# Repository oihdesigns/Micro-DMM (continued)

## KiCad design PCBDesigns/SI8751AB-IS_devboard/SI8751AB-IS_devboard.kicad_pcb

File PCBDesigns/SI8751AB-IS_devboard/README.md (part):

# Si8751 AC/DC development board — revision C

KiCad 10 bench prototype targeting **120 V RMS AC / 170 V DC, less than 1 A**, initially with resistive loads. Two SI8751AB-IS drivers operate back-to-back STP12N60M2 MOSFETs. **AMC3330DWER** measures switched voltage with integrated isolated power; **ACS725LLCTR-05AB-T** measures bidirectional load current. The entire board uses one regulated 3.3 V input. All resistors and capacitors are **0805**. The board is two layers, 110 × 90 mm, for 1.6 mm FR-4 and 35 µm copper.

Open `SI8751AB-IS_devboard.kicad_pro`. Reload schematic and board if an earlier revision is still open. Local symbols and footprints, a schematic PDF, BOM, and validation reports/previews are included. Prototype Gerbers and drills are in `fabrication/revC/`. `revision_B_before_3V3_sensor.zip` preserves revision B; the earlier revision A backup is also retained. The inventory workbook was read without modification; existing project preferences were preserved.

## Changes from revision B

- Replaced ACS712-05B with **ACS725LLCTR-05AB-T**, powered from +3V3.
- Removed the 5 V net. J1-7 is **NC**, preserving all other revision B header pin numbers.
- Removed R15/R16, the 2:1 current-output divider. J1-8 now receives the sensor output directly.
- C17 remains 100 nF; the ACS725 internal filter resistance gives approximately 884 Hz bandwidth. C18 is a direct 1 nF output load.
- Current conversion at nominal supply is now **I = (Vout − 1.65 V) / 0.264 V/A**.
- All passives remain 0805. The ACS725 was not found in the supplied purchase history and is a new procurement item.

## Earlier changes: revision A to B

- Added ACS712-05B between Q2 drain and J3 line. Positive current flows toward the load.
- Replaced AMC0330R with AMC3330. Removed SCT01F03S05, TPS70933 and the converter slot. U3/U4 and C9/C10 references are retired.
- Expanded J1 from 5 to 10 pins. **Pin 5 changed from ground to OUTN.** Voltage-interface firmware scaling also changed.
- Added regulated 5 V input, current filtering, 2:1 current-output attenuation, and AMC diagnostic output.
- Changed voltage divider to stocked 1 MΩ / 15 kΩ parts and EN pull-downs to stocked 75 kΩ parts.
- Corrected plated-pad solder-mask serialization in the generator; both mask openings are verified in the saved board.

## Connections

| Pin | Function |
|---|---|
| J1-1 | Regulated +3.3 V input; provide at least 100 mA capacity |
| J1-2 | Logic ground |
| J1-3 | EN, 3.3 V active high; both MOSFETs commanded together |
| J1-4 | VOUT_P, AMC positive differential output |
| J1-5 | VOUT_N, AMC negative differential output; **not ground** |
| J1-6 | Logic ground |
| J1-7 | NC, no connection; formerly the 5 V input in revision B |
| J1-8 | IOUT_ADC, direct ACS725 output referenced to logic ground |
| J1-9 | DIAG_N, AMC status, 10 kΩ pull-up to 3.3 V; LOW means invalid measurement |
| J1-10 | Logic ground |
| J2-1 / J2-2 | Source line / source return |
| J3-1 / J3-2 | Switched line / load return |

The regulated 3.3 V supply returns to GND_LOGIC, which must remain separate from GND_LOAD_RETURN and SOURCE_FLOAT. The ACS725 requires 3.0–3.6 V; do not power the board from 5 V. Power the host ADC with the board to avoid back-powering an unpowered ADC through the current output. J1-7 is unused; supply power at J1-1.

J2/J3 are Wuerth **691311400102**, 7.62 mm headers. Two **691351400002** cable plugs are additional assembly items outside the fitted PCB BOM. [Wuerth mating series](https://www.we-online.com/en/components/products/TBL_7_62_3514_VERTICAL_69135140000X).

## Switching circuit

```text
J2 LINE -- D Q1 S -- SOURCE_FLOAT -- S Q2 D -- ACS725 IP+ to IP- -- J3 LINE
             G1                         G2
             |                          |
          U1 GATE                    U2 GATE
          U1 SOURCE ---- SOURCE_FLOAT --- U2 SOURCE
J2 RETURN ---------------- GND_LOAD_RETURN -------------------- J3 RETURN
```

Opposing body diodes block either polarity when both gates are off. Driver gate outputs are separate. R1/R3 are 100 Ω input resistors, R2/R4 are 75 kΩ default-off pull-downs, and R5/R6 set TT to 10 kΩ. C3/C4 are 10 pF, 1 kV C0G drain-to-MCAP1 capacitors; MCAP2 is unused. A conventional gate/source bleed resistor would overload the weak generated gate supply and is omitted. [Skyworks datasheet](https://www.skyworksinc.com/-/media/SkyWorks/SL/documents/public/data-sheets/Si8751-2.pdf).

Q1/Q2 are 600 V STP12N60M2, TO-220, pins 1=G, 2=D, 3=S. Tabs are live drains at different potentials; do not attach both directly to one conductive heatsink. At 1 A and 0.45 Ω per MOSFET, combined conduction loss is about 0.9 W at the specified 10 V gate drive. Actual VGS, transition time and dissipation need measurement because driver output is load dependent. Begin at no more than one full on/off cycle per second. [ST part information](https://www.st.com/en/power-transistors/stp12n60m2.html).

## Voltage measurement

U5 receives 3.3 V on its logic side and generates isolated power internally. Its high-side reference connects to load return. OUTP/OUTN have differential gain 2 and need a differential ADC or external difference amplifier. This is not the old ratiometric output. Keep ADC wiring short: direct capacitive load limits are 500 pF per output to ground or 250 pF differential. The ADC must accept approximately 1.44 V output common mode. [TI AMC3330 datasheet](https://www.ti.com/lit/ds/symlink/amc3330.pdf).

R10–R12 are 1 MΩ each; R13 is 15 kΩ, all 0.1%. C14 is 1 nF. Nominal conversion:

```text
divider = (3,000,000 + 15,000) / 15,000 = 201
Vrail = 100.5 × (VOUT_P − VOUT_N)
```

| Calculated quantity | Nominal value |
|---|---:|
| Sense input at 120 V RMS sine | 0.8443 V peak |
| Sense input at 132 V RMS sine (+10% check) | 0.9288 V peak |
| Sense input at 170 V DC | 0.8458 V |
| Divider range for ±1 V linear AMC input | ±201 V instantaneous |
| Each top resistor at 132 V RMS | 61.92 V peak, 1.917 mW average |
| Divider current at 120 V RMS | 39.80 µA RMS |
| Divider / C14 pole | 10.66 kHz |

The 132 V calculation is a margin check, not a higher operating rating. RG2012 top resistors have a 150 V limiting element rating and 0.125 W regular power rating. Three parts share voltage; do not replace them with one 0805. [Susumu RG specification](https://www.susumu.co.jp/common/pdf/e_all.pdf).

C5/C6/C19 bypass DCDC_OUT/HLDO_IN; C7/C8 bypass HLDO_OUT; C11/C12 bypass VDD; C13 bypasses DCDC_IN/LDO_OUT. Use low-ESR ceramics with adequate effective capacitance under DC bias. No external LDO load or ferrite beads are fitted. EMI performance remains unqualified.

DIAG_N LOW invalidates measurements. Startup, loss of power or a zero reading does not establish that the rail is safe to touch. Calibrate zero/gain. For RMS, square calibrated instantaneous samples, average over complete cycles, then take the square root. Subtract the mean only for AC-only RMS.

## Current measurement

U6 is ACS725LLCTR-05AB-T, a 3.3 V, ±5 A bidirectional Hall sensor. Its analog output connects directly to J1-8 with no attenuation. At nominal 3.3 V supply:

```text
IOUT_ADC = 1.65 V + 0.264 V/A × I
I = (IOUT_ADC − 1.65 V) / 0.264 V/A
```

At ±1 A DC, output is 1.386–1.914 V. At 1 A RMS sine it moves ±0.3734 V about zero-current level. Nominal ±5 A span is 0.33–2.97 V, while the board load target remains below 1 A. ADC signal sensitivity is approximately 2.85 times revision B's divided output.

C17=100 nF and the nominal internal 1.8 kΩ resistance give a pole near 884 Hz, approximately 0.23% attenuation and 3.9° phase lag at 60 Hz. C18=1 nF is a direct output load. Total output capacitance, including the cable and ADC, must remain at or below 10 nF; DC load resistance must be at least 4.7 kΩ. Keep the ADC connection short and qualify its sampling-settling behavior. [Allegro ACS725 datasheet](https://www.allegromicro.com/-/media/files/datasheets/acs725-datasheet.ashx).

Calibrate zero with no current and gain against a known current. The formula assumes nominal supply: both zero and sensitivity vary with supply and temperature, so calibration at the actual operating supply is preferred. Do not assume simple ideal ratiometric cancellation removes every gain error. Offset and noise remain significant below 1 A. Characterize or compensate the filter phase response before power-factor or real-power measurements. This circuit monitors current; it does not implement hardware overcurrent shutdown.

The sensor pin functions match the earlier SOIC-8 part: 1/2 IP+, 3/4 IP−, 5 ground, 6 FILTER, 7 output, 8 supply. It cannot be fitted to an unmodified revision B assembly powered at 5 V. Use revision C supply wiring, component population and firmware scaling.

## Inventory and assembly

`BOM_inventory.csv` records MPNs, workbook row numbers, historical quantities and unmatched parts. **28 of 37 fitted references match exact MPNs.** U5 has the stocked automotive alternative **AMC3330QDWERQ1**: its DWE footprint, pin functions, integrated power and gain suit this design. Use its separate error/temperature specifications when qualifying that assembly. [TI automotive variant](https://www.ti.com/lit/ds/symlink/amc3330-q1.pdf).

Source: `C:\Users\Nick\Dropbox (Personal)\AvaliableParts\Combined_parts_DigiKey_and_Mouser.xlsx`, sheet `Combined parts`. Quantities describe purchase history, not verified remaining stock; repeated references consume shared stock.

| Items not found as exact inventory matches | Needed per board |
|---|---:|
| STP12N60M2 | 2 |
| ACS725LLCTR-05AB-T | 1 |
| C0805C100JDGACTU, 10 pF / 1 kV C0G | 2 |
| 691311400102 terminal header | 2 |
| 1×10, 2.54 mm vertical control header | 1 |
| AMC3330DWER, if stocked Q1 alternative is not used | 1 |

Cable plugs, an external fuse/holder and insulating mounting hardware are additional. Stocked 20–50 V MOSFETs are unsuitable for this voltage target.

## Layout and validation

Load-current traces are 0.8–1.0 mm wide; signal branches are 0.3 mm. High-voltage nodes use 0.8 mm copper clearance, the floating gate domain 0.3 mm, and logic-to-field copper 2.5 mm. There is no converter exception or slot. ACS IP+ and IP− are internally joined through a milliohm conductor, so mutual clearance is 0.3 mm; this exception never applies across its isolation barrier. TO-220 pads retain 1.1 mm drills with 1.65 mm copper width, giving 0.89 mm adjacent clearance. Four 3.2 mm mounting holes are included.

See `validation/revC_erc.rpt` and `validation/revC_drc.rpt` for ERC, DRC and schematic/PCB parity. Schematic, copper plot and board render are visually reviewed. These checks establish CAD consistency, not hardware performance or mains certification.

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
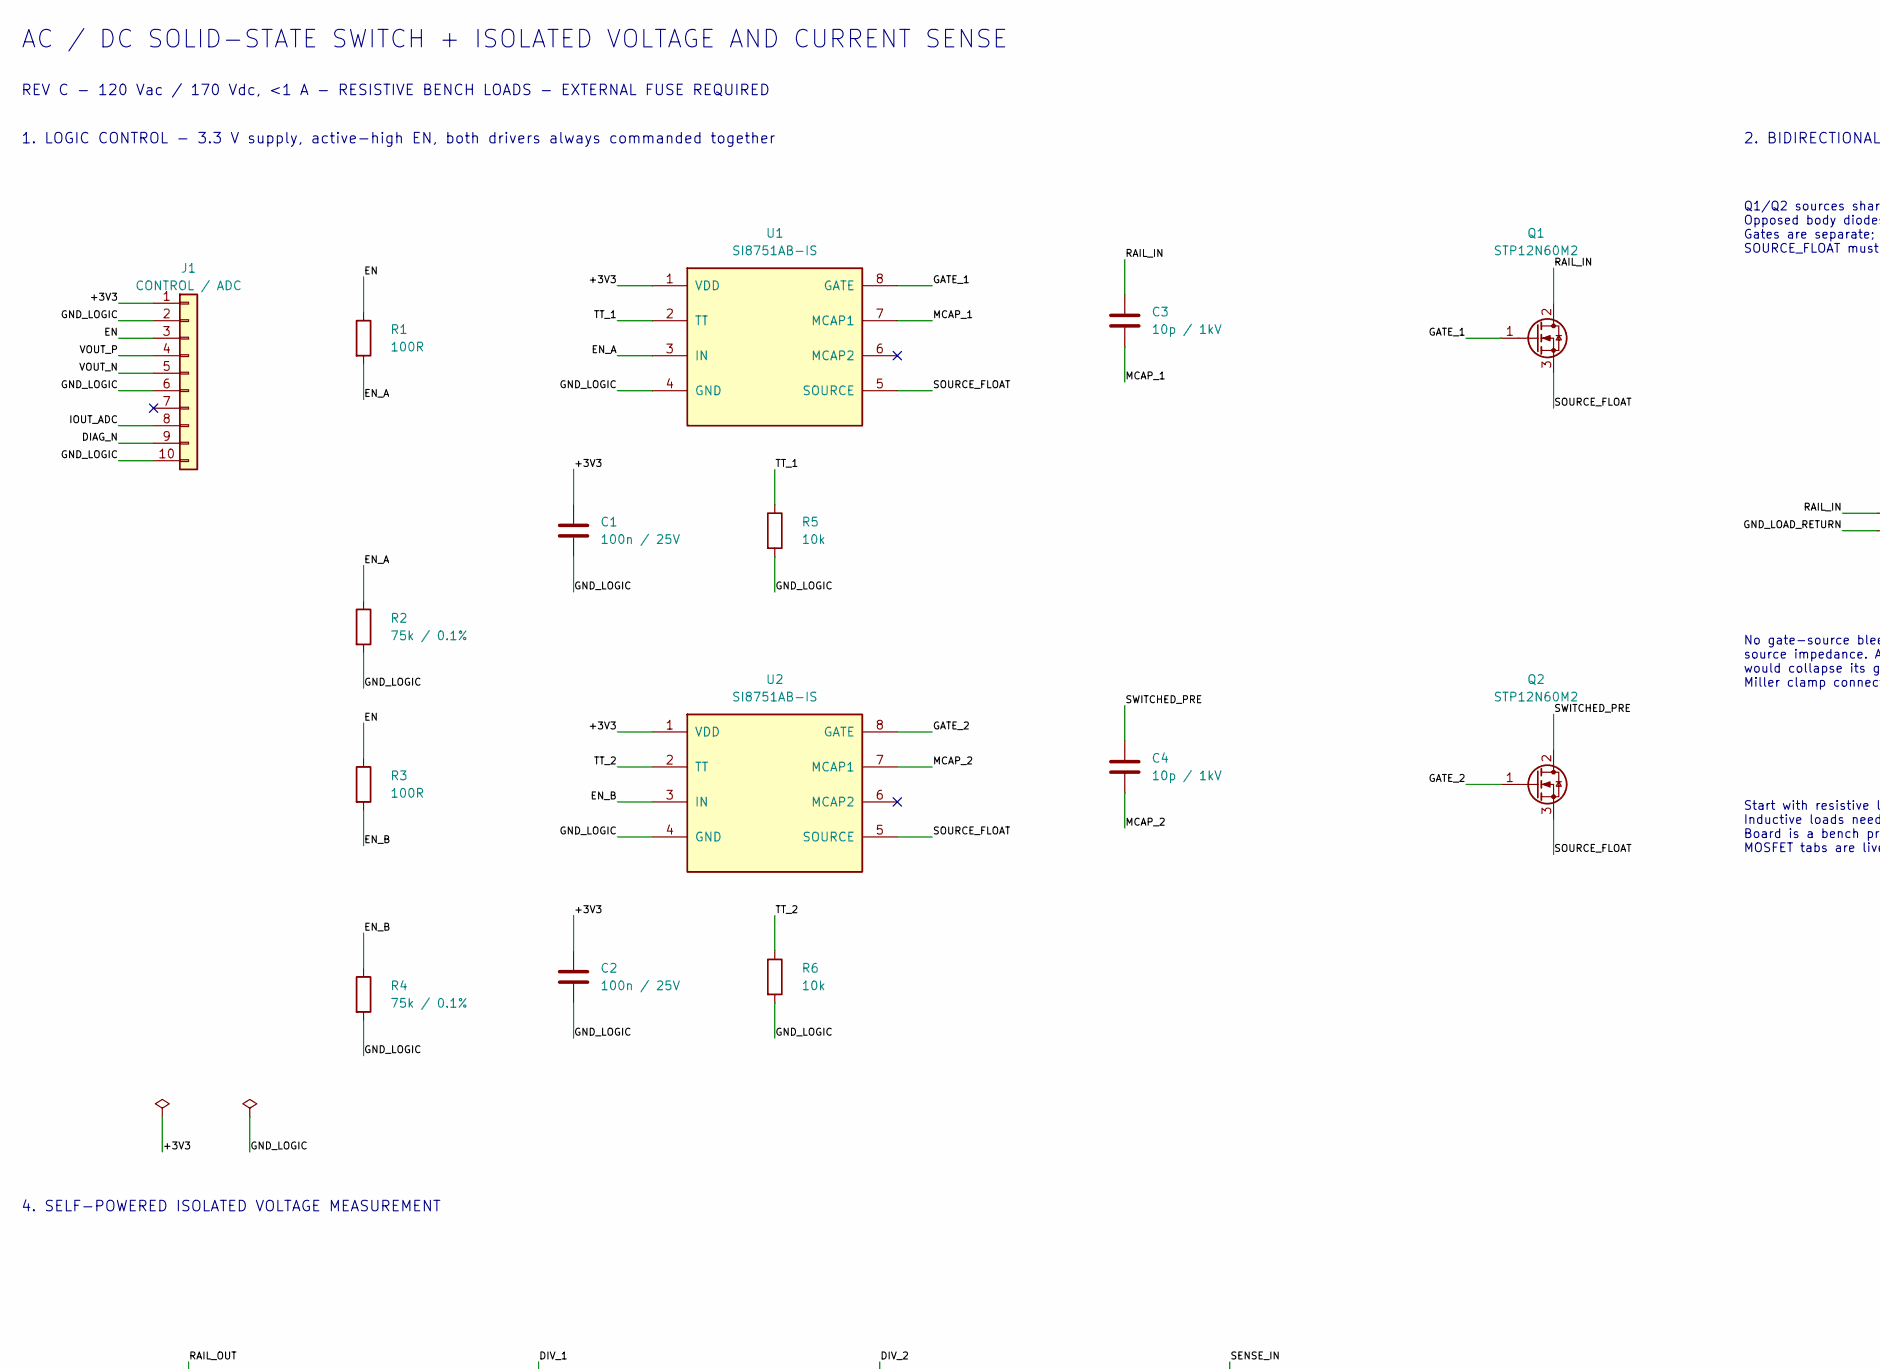
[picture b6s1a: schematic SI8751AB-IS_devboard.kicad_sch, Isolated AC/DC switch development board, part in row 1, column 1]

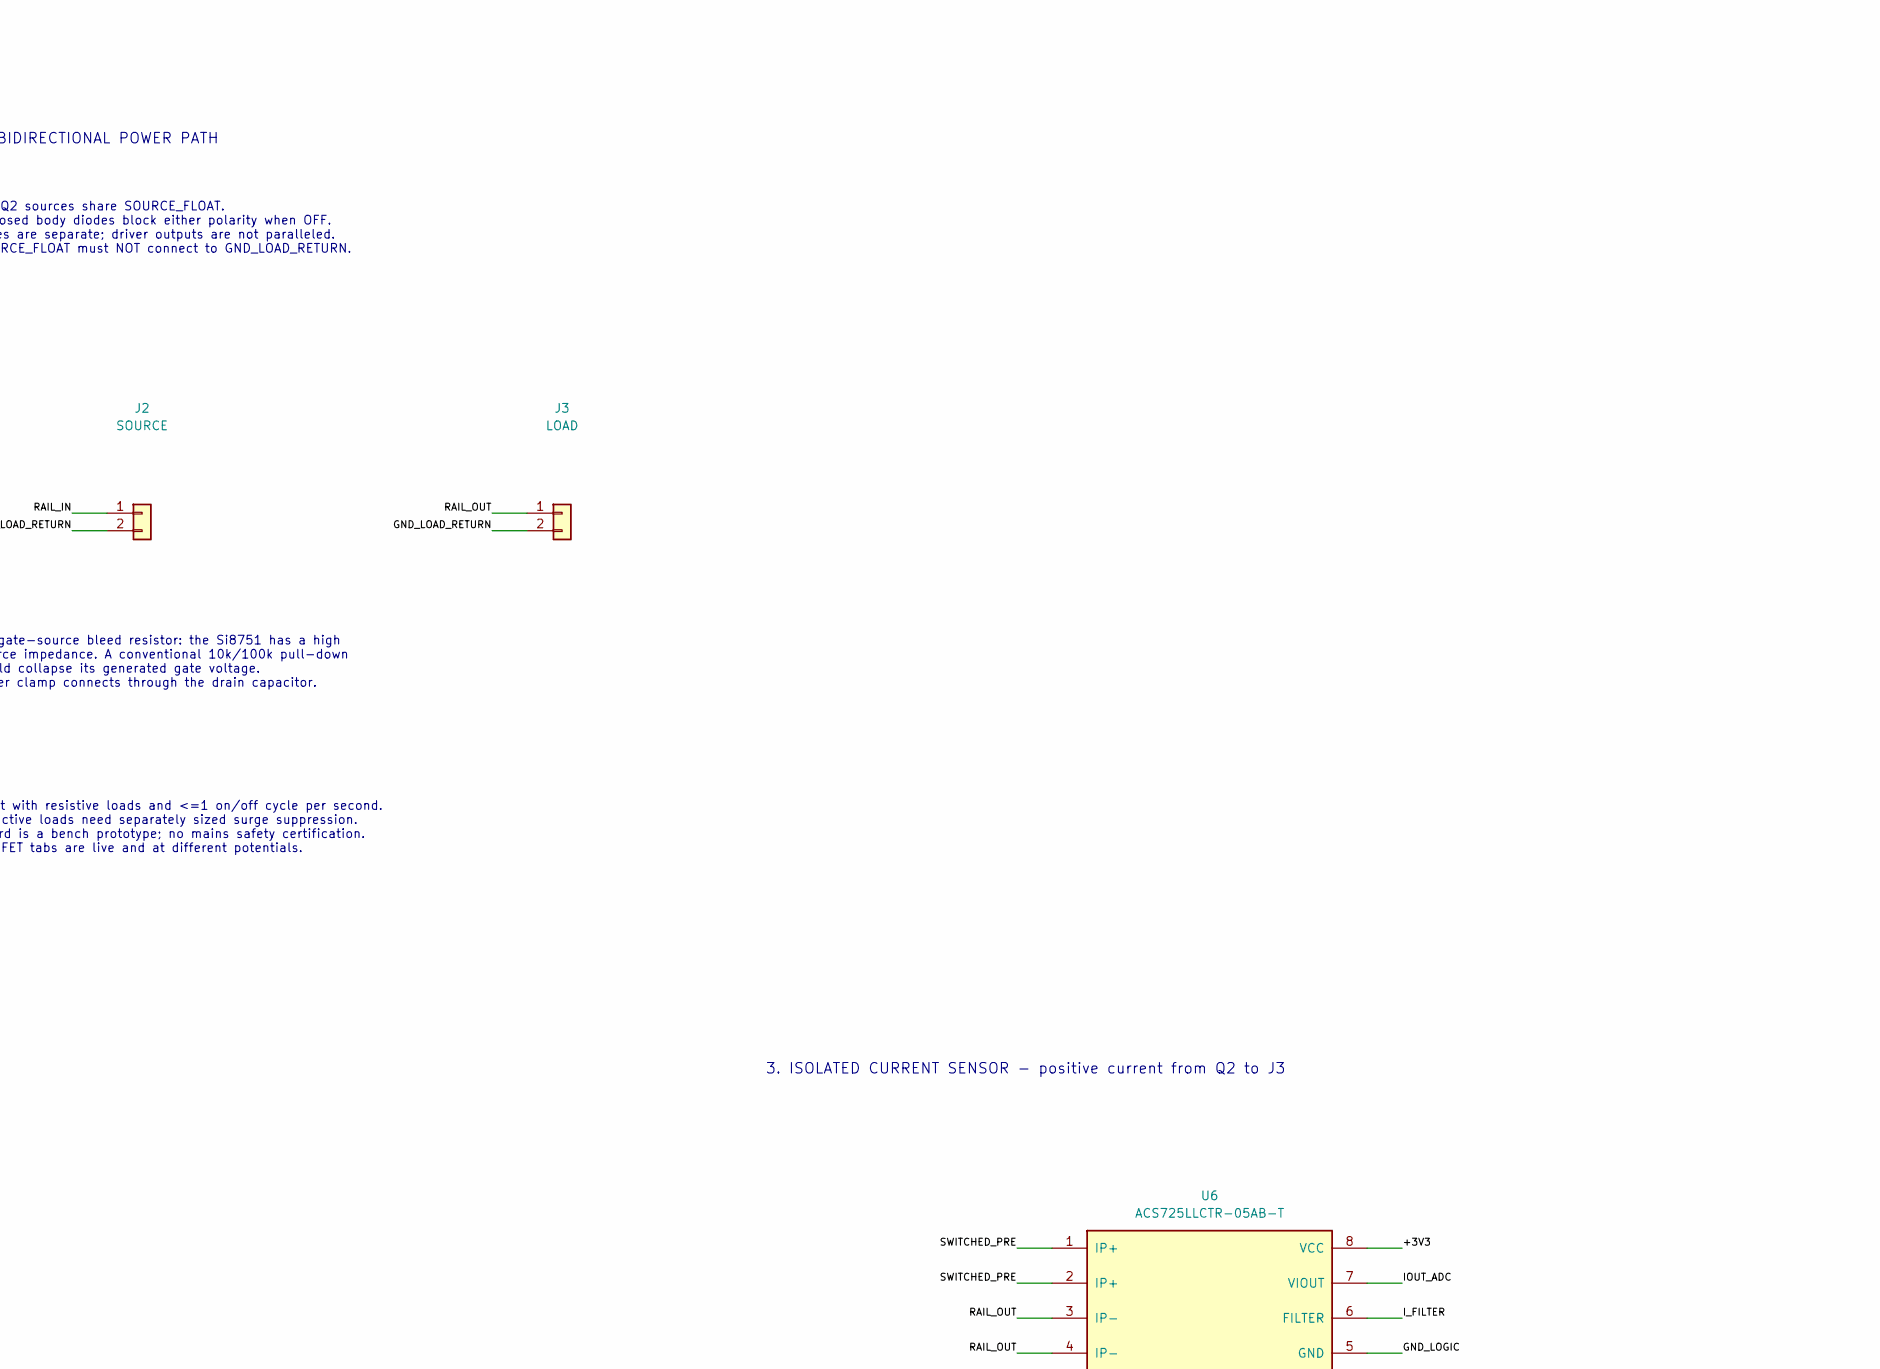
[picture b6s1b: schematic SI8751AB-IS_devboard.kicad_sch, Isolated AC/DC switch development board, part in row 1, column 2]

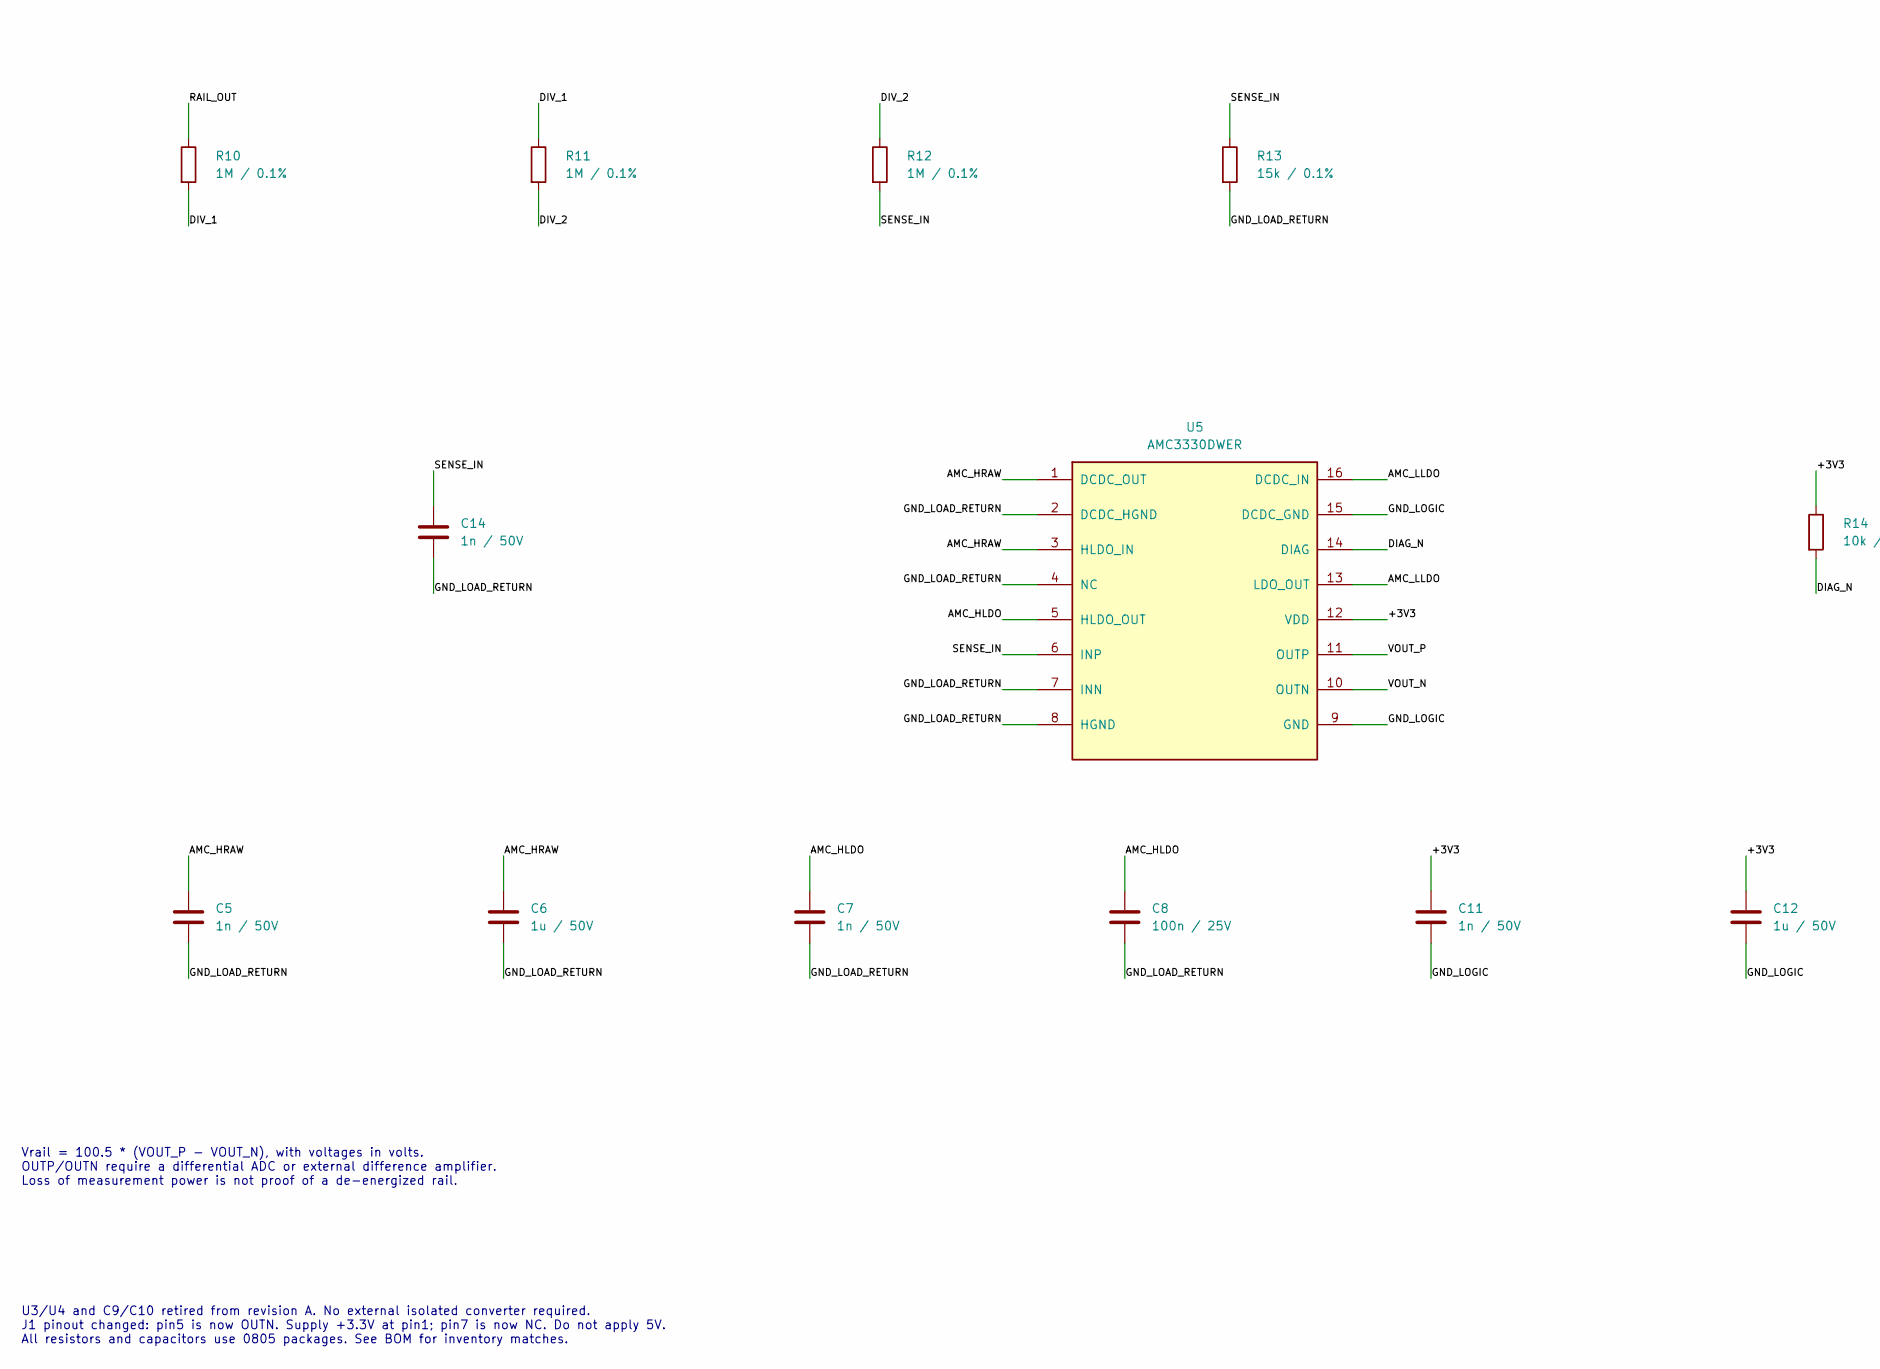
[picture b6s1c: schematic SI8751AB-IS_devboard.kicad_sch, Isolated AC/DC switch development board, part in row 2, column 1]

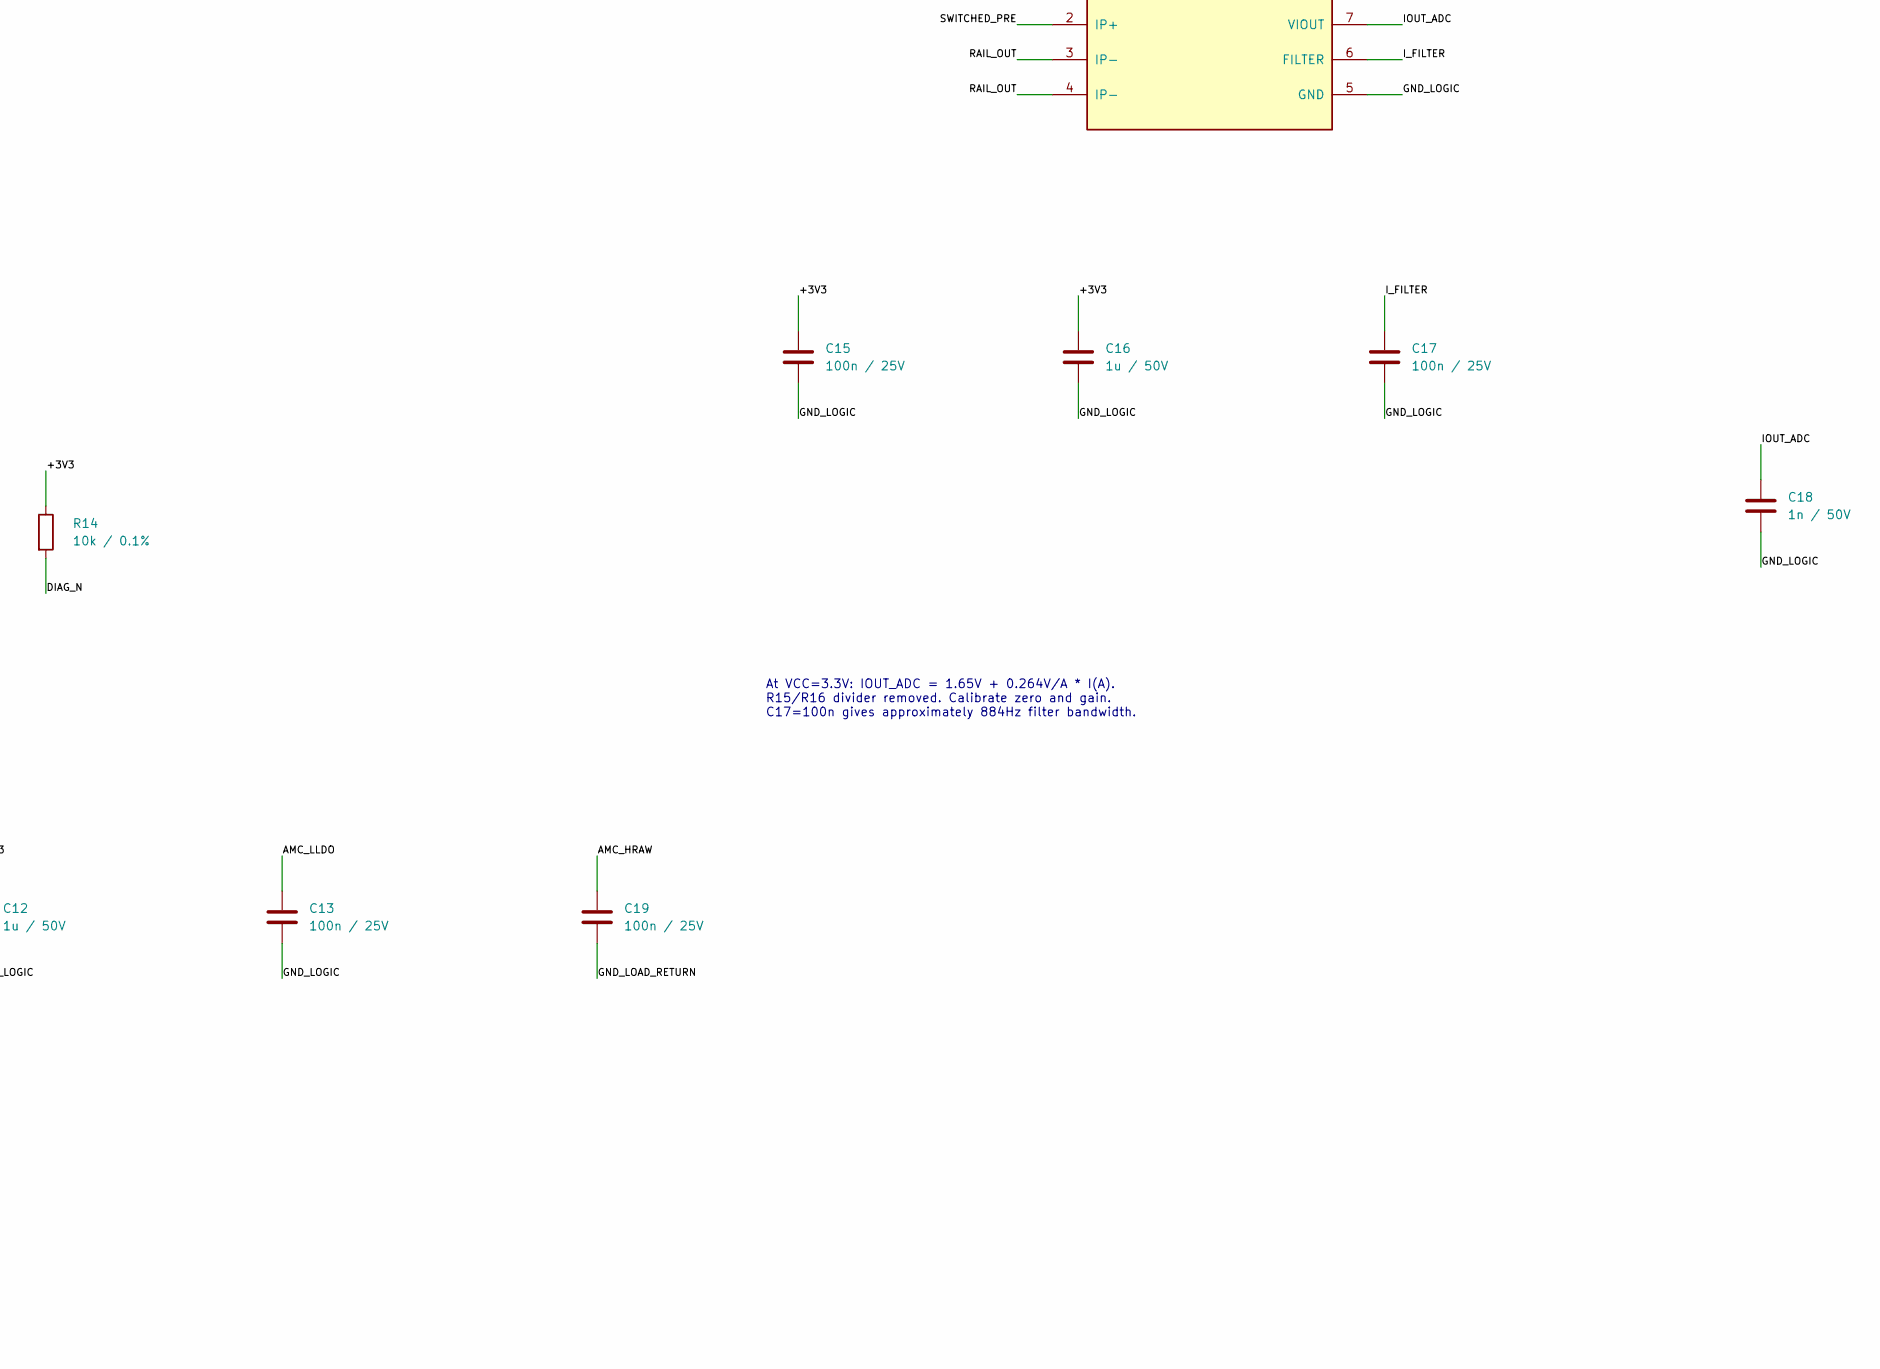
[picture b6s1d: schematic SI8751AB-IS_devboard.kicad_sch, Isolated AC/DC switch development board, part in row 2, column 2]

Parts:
C1, C2, C8, C13, C15, C17, C19: 100n / 25V; C_0805_2012Metric
C3, C4: 10p / 1kV; C_0805_2012Metric
C5, C7, C11, C14, C18: 1n / 50V; C_0805_2012Metric
C6, C12, C16: 1u / 50V; C_0805_2012Metric
J1: CONTROL / ADC; PinHeader_1x10_P2.54mm_Vertical
J2: SOURCE; Wuerth_691311400102_P7.62mm
J3: LOAD; Wuerth_691311400102_P7.62mm
Q1, Q2: STP12N60M2; TO-220-3_Vertical
R1, R3: 100R; R_0805_2012Metric
R2, R4: 75k / 0.1%; R_0805_2012Metric
R5, R6: 10k; R_0805_2012Metric
R10, R11, R12: 1M / 0.1%; R_0805_2012Metric
R13: 15k / 0.1%; R_0805_2012Metric
R14: 10k / 0.1%; R_0805_2012Metric
U1, U2: SI8751AB-IS; SOIC-8_3.9x4.9mm_P1.27mm
U5: AMC3330DWER; SOIC-16W_7.5x10.3mm_P1.27mm
U6: ACS725LLCTR-05AB-T; SOIC-8_3.9x4.9mm_P1.27mm

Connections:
/+3V3: C1.1, C2.1, C11.1, C12.1, C15.1, C16.1, J1.1, R14.1, U1.1 (VDD), U2.1 (VDD), U5.12 (VDD), U6.8 (VCC)
/AMC_HLDO: C7.1, C8.1, U5.5 (HLDO_OUT)
/AMC_HRAW: C5.1, C6.1, C19.1, U5.1 (DCDC_OUT), U5.3 (HLDO_IN)
/AMC_LLDO: C13.1, U5.13 (LDO_OUT), U5.16 (DCDC_IN)
/DIAG_N: J1.9, R14.2, U5.14 (DIAG)
/DIV_1: R10.2, R11.1
/DIV_2: R11.2, R12.1
/EN: J1.3, R1.1, R3.1
/EN_A: R1.2, R2.1, U1.3 (IN)
/EN_B: R3.2, R4.1, U2.3 (IN)
/GATE_1: Q1.1 (G), U1.8 (GATE)
/GATE_2: Q2.1 (G), U2.8 (GATE)
/GND_LOAD_RETURN: C5.2, C6.2, C7.2, C8.2, C14.2, C19.2, J2.2, J3.2, R13.2, U5.2 (DCDC_HGND), U5.4 (NC), U5.7 (INN), U5.8 (HGND)
/GND_LOGIC: C1.2, C2.2, C11.2, C12.2, C13.2, C15.2, C16.2, C17.2, C18.2, J1.2, J1.6, J1.10, R2.2, R4.2, R5.2, R6.2, U1.4 (GND), U2.4 (GND), U5.9 (GND), U5.15 (DCDC_GND), U6.5 (GND)
/IOUT_ADC: C18.1, J1.8, U6.7 (VIOUT)
/I_FILTER: C17.1, U6.6 (FILTER)
/MCAP_1: C3.2, U1.7 (MCAP1)
/MCAP_2: C4.2, U2.7 (MCAP1)
/RAIL_IN: C3.1, J2.1, Q1.2 (D)
/RAIL_OUT: J3.1, R10.1, U6.3 (IP-), U6.4 (IP-)
/SENSE_IN: C14.1, R12.2, R13.1, U5.6 (INP)
/SOURCE_FLOAT: Q1.3 (S), Q2.3 (S), U1.5 (SOURCE), U2.5 (SOURCE)
/SWITCHED_PRE: C4.1, Q2.2 (D), U6.1 (IP+), U6.2 (IP+)
/TT_1: R5.1, U1.2 (TT)
/TT_2: R6.1, U2.2 (TT)
/VOUT_N: J1.5, U5.10 (OUTN)
/VOUT_P: J1.4, U5.11 (OUTP)

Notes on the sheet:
AC / DC SOLID-STATE SWITCH + ISOLATED VOLTAGE AND CURRENT SENSE
REV C - 120 Vac / 170 Vdc, <1 A - RESISTIVE BENCH LOADS - EXTERNAL FUSE REQUIRED
1. LOGIC CONTROL - 3.3 V supply, active-high EN, both drivers always commanded together
2. BIDIRECTIONAL POWER PATH
Q1/Q2 sources share SOURCE_FLOAT. Opposed body diodes block either polarity when OFF. Gates are separate; driver outputs are not paralleled. SOURCE_FLOAT must NOT connect to GND_LOAD_RETURN.
No gate-source bleed resistor: the Si8751 has a high source impedance. A conventional 10k/100k pull-down would collapse its generated gate voltage. Miller clamp connects through the drain capacitor.
Start with resistive loads and <=1 on/off cycle per second. Inductive loads need separately sized surge suppression. Board is a bench prototype; no mains safety certification. MOSFET tabs are live and at different potentials.
3. ISOLATED CURRENT SENSOR - positive current from Q2 to J3
At VCC=3.3V: IOUT_ADC = 1.65V + 0.264V/A * I(A). R15/R16 divider removed. Calibrate zero and gain. C17=100n gives approximately 884Hz filter bandwidth.
4. SELF-POWERED ISOLATED VOLTAGE MEASUREMENT
Vrail = 100.5 * (VOUT_P - VOUT_N), with voltages in volts. OUTP/OUTN require a differential ADC or external difference amplifier. Loss of measurement power is not proof of a de-energized rail.
U3/U4 and C9/C10 retired from revision A. No external isolated converter required. J1 pinout changed: pin5 is now OUTN. Supply +3.3V at pin1; pin7 is now NC. Do not apply 5V. All resistors and capacitors use 0805 packages. See BOM for inventory matches.

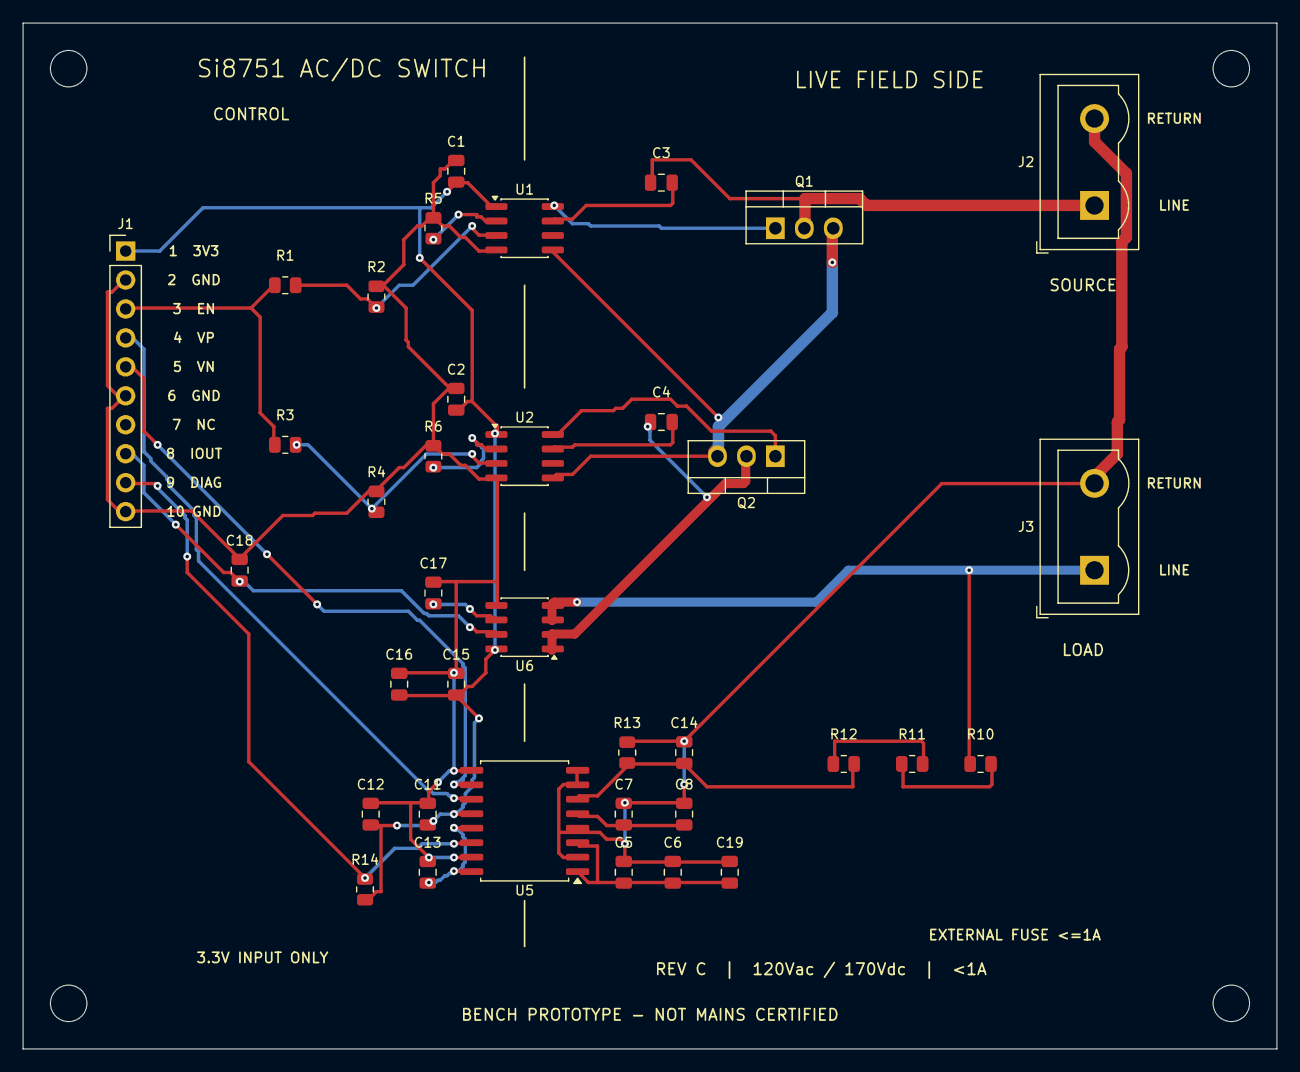
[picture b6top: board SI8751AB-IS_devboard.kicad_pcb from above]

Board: 2 copper layers, 110.0 x 90.0 mm, 41 parts (0 on the bottom side), 27 nets.

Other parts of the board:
H1, H2, H3, H4: MountingHole_3.2mm_M3

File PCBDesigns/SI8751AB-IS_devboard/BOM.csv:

reference,value,manufacturer_part_number,stocked_alternative,inventory_match,inventory_sheet_row,historical_quantity,footprint,purpose,datasheet
J1,CONTROL / ADC,Generic 1x10 2.54mm vertical header,,Not found in purchase history,,,Devboard:PinHeader_1x10_P2.54mm_Vertical,Rev C: 3.3V only; pin7 NC (formerly 5V); current output is no longer divided,
R1,100R,RNCF0805DTE100R,,Exact MPN,123,50,Devboard:R_0805_2012Metric,Series input damping,
R2,75k / 0.1%,ERA-6AEB753V,,Exact MPN,139,50,Devboard:R_0805_2012Metric,Default OFF; stocked ERA-6AEB753V,
R3,100R,RNCF0805DTE100R,,Exact MPN,123,50,Devboard:R_0805_2012Metric,Series input damping,
R4,75k / 0.1%,ERA-6AEB753V,,Exact MPN,139,50,Devboard:R_0805_2012Metric,Default OFF; stocked ERA-6AEB753V,
U1,SI8751AB-IS,SI8751AB-IS,,Exact MPN,90,10,Devboard:SOIC-8_3.9x4.9mm_P1.27mm,One isolated gate driver per MOSFET,https://www.skyworksinc.com/-/media/SkyWorks/SL/documents/pu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
C1,100n / 25V,CL21B104KACNNNC,,Exact MPN,17,200,Devboard:C_0805_2012Metric,Place beside driver VDD / GND,
R5,10k,RN73H2ATTD1002B25,,Exact MPN,121,50,Devboard:R_0805_2012Metric,TT=10k: 9V minimum unloaded gate output; qualify actual VGS under load,
C3,10p / 1kV,C0805C100JDGACTU,,Not found in purchase history,,,Devboard:C_0805_2012Metric,0805 C0G 1kV; qualify dV/dt <=600V/us for 6mA MCAP limit,
Q1,STP12N60M2,STP12N60M2,,Not found in purchase history,,,Devboard:TO-220-3_Vertical,600V NMOS; RDSon specified at 10V; qualify VGS and dissipation on prototype,https://www.st.com/resource/en/datasheet/stp12n60m2.pdf
U2,SI8751AB-IS,SI8751AB-IS,,Exact MPN,90,10,Devboard:SOIC-8_3.9x4.9mm_P1.27mm,One isolated gate driver per MOSFET,https://www.skyworksinc.com/-/media/SkyWorks/SL/documents/pu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
C2,100n / 25V,CL21B104KACNNNC,,Exact MPN,17,200,Devboard:C_0805_2012Metric,Place beside driver VDD / GND,
R6,10k,RN73H2ATTD1002B25,,Exact MPN,121,50,Devboard:R_0805_2012Metric,TT=10k: 9V minimum unloaded gate output; qualify actual VGS under load,
C4,10p / 1kV,C0805C100JDGACTU,,Not found in purchase history,,,Devboard:C_0805_2012Metric,0805 C0G 1kV; qualify dV/dt <=600V/us for 6mA MCAP limit,
Q2,STP12N60M2,STP12N60M2,,Not found in purchase history,,,Devboard:TO-220-3_Vertical,600V NMOS; RDSon specified at 10V; qualify VGS and dissipation on prototype,https://www.st.com/resource/en/datasheet/stp12n60m2.pdf
J2,SOURCE,691311400102,,Not found in purchase history,,,Devboard:Wuerth_691311400102_P7.62mm,"Wuerth 691311400102, 7.62mm; feed through external appropriately rated <=1A fuse",
J3,LOAD,691311400102,,Not found in purchase history,,,Devboard:Wuerth_691311400102_P7.62mm,Switched line / unswitched return; resistive loads initially,
U6,ACS725LLCTR-05AB-T,ACS725LLCTR-05AB-T,,Not found in purchase history,,,Devboard:SOIC-8_3.9x4.9mm_P1.27mm,3.3V supply; 264mV/A nominal; zero-current output VCC/2; isolated series current conductor,https://www.allegromicro.com/-/media/files/datasheets/acs725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
C15,100n / 25V,CL21B104KACNNNC,,Exact MPN,17,200,Devboard:C_0805_2012Metric,ACS VCC bypass,
C16,1u / 50V,CL21B105KBFNNNE,,Exact MPN,15,100,Devboard:C_0805_2012Metric,ACS VCC bulk,
C17,100n / 25V,CL21B104KACNNNC,,Exact MPN,17,200,Devboard:C_0805_2012Metric,Internal 1.8k plus 100n: approximately 884Hz pole,
C18,1n / 50V,C0805C102K5HACAUTO,,Exact MPN,14,120,Devboard:C_0805_2012Metric,Direct output load; total output capacitance <=10nF and DC load >=4.7k; qualify host ADC settling,
R10,1M / 0.1%,RG2012P-105-B-T5,,Exact MPN,120,50,Devboard:R_0805_2012Metric,"RG2012P-105-B-T5; 0805, 150V limiting element voltage, 0.125W",
R11,1M / 0.1%,RG2012P-105-B-T5,,Exact MPN,120,50,Devboard:R_0805_2012Metric,"RG2012P-105-B-T5; 0805, 150V limiting element voltage, 0.125W",
R12,1M / 0.1%,RG2012P-105-B-T5,,Exact MPN,120,50,Devboard:R_0805_2012Metric,"RG2012P-105-B-T5; 0805, 150V limiting element voltage, 0.125W",
R13,15k / 0.1%,RG2012P-153-B-T5,,Exact MPN,124,50,Devboard:R_0805_2012Metric,RG2012P-153-B-T5; divider factor 201; input 0.8443Vpk at 120Vac,
U5,AMC3330DWER,AMC3330DWER,AMC3330QDWERQ1,Compatible automotive variant; see README,92,10,Devboard:SOIC-16W_7.5x10.3mm_P1.27mm,Integrated isolated DC/DC; fixed differential gain 2; stocked AMC3330QDWERQ1 is an assembly alternative,https://www.ti.com/lit/ds/symlink/amc3330.pdf
C5,1n / 50V,C0805C102K5HACAUTO,,Exact MPN,14,120,Devboard:C_0805_2012Metric,DCDC_OUT pin1 / DCDC_HGND pin2 HF bypass,
C6,1u / 50V,CL21B105KBFNNNE,,Exact MPN,15,100,Devboard:C_0805_2012Metric,DCDC_OUT bulk; 1u effective target,
C19,100n / 25V,CL21B104KACNNNC,,Exact MPN,17,200,Devboard:C_0805_2012Metric,HLDO_IN local bypass at pin3; no ferrite beads fitted,
C7,1n / 50V,C0805C102K5HACAUTO,,Exact MPN,14,120,Devboard:C_0805_2012Metric,HLDO_OUT HF bypass,
C8,100n / 25V,CL21B104KACNNNC,,Exact MPN,17,200,Devboard:C_0805_2012Metric,HLDO_OUT bypass; no external load,
C11,1n / 50V,C0805C102K5HACAUTO,,Exact MPN,14,120,Devboard:C_0805_2012Metric,VDD HF bypass,
C12,1u / 50V,CL21B105KBFNNNE,,Exact MPN,15,100,Devboard:C_0805_2012Metric,VDD bulk; 1u effective target,
C13,100n / 25V,CL21B104KACNNNC,,Exact MPN,17,200,Devboard:C_0805_2012Metric,DCDC_IN pin16 to DCDC_GND pin15; no external load,
C14,1n / 50V,C0805C102K5HACAUTO,,Exact MPN,14,120,Devboard:C_0805_2012Metric,Input filter: approximately 10.7kHz; return at AMC INN,
R14,10k / 0.1%,RN73H2ATTD1002B25,,Exact MPN,121,50,Devboard:R_0805_2012Metric,Active-low open-drain diagnostic pullup; LOW means invalid measurement,

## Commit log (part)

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2025-06-22 Current Version as of Github Setup
    Something of an Advanced Beta
2025-06-22 Current User Manual
    Initial Git Upload
2025-06-22 Initial Serial Terminal Upload
2025-06-22 Collected Spreadsheets
    BOM, Measurement Math, and Calibrations.
2025-06-22 KiCad Design Files
    Initial Git Upload
2025-06-22 Renaming the main file test
2025-06-22 Broke EEPROM Cals out to their own tab
2025-06-22 Adjusted Resistor Null Offset and Digit Display
2025-06-22 Adding LTSpice Models of the Analog Ciruits
2025-06-22 LTSpice files into their own folder
2025-06-23 Added a "Hold Value" display option
    Now you can hold a value with the "type" button. It only types the value when you're in "type" mode.
2025-06-23 Added a "High Resistance" Mode
    This is a mode for measurements over 1M Ohms. Some of the auto power save / screen comfort settings assume the circuit is open at a threshold set below the theoretical max to avoid noise triggers. Th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
2025-06-25 Cleaning Aux Files
2025-06-25 Adding some photos
2025-06-25 Updated current reading code.
    Updated formatting of current reading mode for better auto-ranging.
2025-06-25 Creating an ESP32 Version
    In progress
2025-06-26 ESP32 EEPROM corrections.
2025-06-26 Added Manual VAC Mode
2025-06-27 Working on a Giga-COmpatible DMM code.
    Also working on adding level shifting to the next PCB design.
2025-06-27 Preserved a Giga version that works on the default (I2C) screen
    Might be useful for testing
2025-06-27 More updates to the next PCB
2025-06-28 More work on the Giga Version
2025-06-28 Working on Giga Files
    And seeing if I can make it work with an ADS1256 for more bits.
2025-06-29 Added Touchscreen Buttons to the Giga Shield Version
    Revised next PCB for power input options
2025-06-29 Added Voltage Plot
2025-06-29 More Button Refinement
2025-06-29 Button Refinement for the Giga Touchscreen
2025-06-30 Further Giga Refinements
2025-07-01 Developing RP2350 Implemetation
2025-07-02 File rearrangement
2025-07-02 Adding USB thumbdrive data logging for Giga
2025-07-04 Better Giga Autolog Implementation
2025-07-04 Starting to make an ADS1256 Version
    And minor XAIO RA4M1 edits
2025-07-04 Giga Auto Data Logging Refinements
2025-07-05 Display Improvements for the Giga Shield
2025-07-05 Couple further refinements
2025-07-05 General Giga Function Improvements
    Using the built-in LED now. Option to plot the resistance readings. Reverting to previous more general version of calibration values.
2025-07-05 Groundwork for simultaneous V&I plots.
2025-07-06 Minor Giga Screen Refinements
2025-07-07 Calibrating the Giga Version
    1256 Version remains completely non functional
2025-07-10 Minor Giga Improvements / File Rearrangement
2025-07-11 Removed DAC, not ready yet. Added loop monitor pin
2025-07-12 Working On Implementing Continuity in the Voltmeter
2025-07-13 The Giga version now can tell between floating or open in voltmeter mode
2025-07-14 Added feature for Giga version to report if 0vdc is due to open leads or same net.
2025-07-14 Moving to the KiCAD 9
2025-07-15 Giga version now shows int reading for float/closed determination.
2025-07-16 Minor float or closed (VAC trigger) adjustment
2025-07-17 Giga Version Refinements, Added white paper on the auto floating probes detect voltmeter design
2025-07-17 Updates to paper following updates
2025-07-19 Minor Edits to Paper
2025-07-22 Implementing function generator/audio alerts over the DACs using second core
2025-07-23 Changed name of paper, minor Giga edits
2025-07-23 Removed previous paper
2025-07-24 Updated RA4M1 Arduino sketch for open-lead sensing
2025-07-26 Revised the audio alerts
2025-07-27 Working on adding headphone control
2025-07-27 Further Refinement of headphones / microphone audio interface
2025-07-31 Mostly working on the next PCB
2025-08-01 Minor PCB Updates
2025-08-02 PCB work
2025-08-04 KiCAD Updates
2025-08-07 Working on things
2025-08-10 Making a Version of Code for Newest PCB Revision
2025-08-10 Update microDMM_RA4M1_XIAO_SMD_V5.ino
    Further adjustments to the program for the new board version.
2025-08-11 Updates to the programming files for the V5 boards
2025-08-12 Minor Giga Updates, Working on a business card size version
2025-08-13 Working on next PCB, mostly.
2025-08-13 Fixed ammeter problem and some nuisance alerts on Giga version
2025-08-14 Edits to the RA4M1 version and KiCAD work
2025-08-15 Minor KiCAD updates and file reorganization
2025-08-17 Arduino Code Updates for a PCB change
2025-08-20 Misc Arduino Files Work
2025-08-24 Working on the next PCBs
2025-08-30 Adjusting the open volt detection and power save logics.
2025-08-30 Debugging XAIO version sleep mode
2025-08-30 Work on next PCB version
2025-09-06 Working on PCBs and Separating Out Different Versions
2025-09-27 Add Raspberry Pi Tkinter UI and logging workflow
2025-09-27 Add Raspberry Pi hardware abstraction and control audit
2025-09-27 Add ADS1256 backend with auto-ranging measurement helpers
2025-09-27 Gathering RPI Port Files
2025-09-27 Add Raspberry Pi runtime harness and setup docs
2025-09-27 Allow running run_pi.py as a standalone script
2025-09-27 Add debug UI harness with configurable channels and GPIO controls
2025-09-27 Minor PCB Revisions
2025-09-27 Fix standalone execution for debug harness
2025-09-27 Add debug measurement mode with runtime clock
2025-09-27 Fix debug voltage display
2025-09-28 Add debug controls for gain, sample rate, and calibration
2025-09-28 Handle missing sample rate attribute in debug view
2025-09-28 Make debug controls panel visible by default
2025-09-28 Make debug controls permanently visible
2025-09-28 Expose ADC controls in Pi UI
2025-09-28 Move ADC controls into dedicated tab
2025-09-29 Moving Files Around
2025-09-30 Working on an FT232H (direct computer interface) version.
2025-10-02 FT232 Chip Updates
2025-10-02 Add FT232H desktop micro-DMM application
2025-10-02 Fix NameError when updating continuity output
2025-10-03 Add advanced ADS1115 controls and restore continuity blink
2025-10-03 Speed up continuity output and add manual pin overrides
2025-10-04 Refine FT232H defaults and bridge voltage visibility
2025-10-04 Add GUI control to clear VAC accumulator
2025-10-04 Restructure GUI layout and add burst logging capture
2025-10-04 Fix RMS buffer to store squared samples
2025-10-04 Stabilize VAC RMS calculation and surface Blinka import errors
2025-10-05 Working on the R Pi version
2025-10-05 Add integrated ADS1256 GUI with DMM math and trigger options
2025-10-05 Fix ADS1256 capture flow and add live view controls
2025-10-05 Restore ADC readings and split live controls
2025-10-11 Add advanced trigger positioning modes
2025-10-11 Calibrate ADS1256 after gain or rate changes
2025-10-12 Updating Program
2025-10-12 Update ADS1256 GUI V3_triggering.py
    Working on calibrations
2025-10-19 Giga Open Lead Detection Revisions & Minor PCB edits
2025-10-22 Expanding the Nano Differential Voltmeter
2025-10-23 Further updates
2025-10-25 Working on a revised instrumentation-focused PCB
2025-10-25 Voltmeter Front End Conditioning PCB
2025-10-25 Learning QSpice
2025-10-26 Finishing PCBs to be made.
2025-11-02 More work on an simulated process controller
2025-11-02 More process controller prototyping
2025-11-08 Working on the open lead detect process controller
2025-11-08 Further process meter w/ open lead detect work
2025-11-09 More Open Lead Process Meter Development
2025-11-09 Additional process meter refinements
2025-11-09 More tests and refinements of the process meter
2025-11-10 Various Minor Changes
2025-11-12 Revised open vs closed reporting to be second order instead of first
2025-11-12 Added a potentiometer for on the fly adjustment of the open lead threshold
2025-11-17 Work on voltmeter open lead detect demo
2025-11-27 New AdaLogger Version and PCB revisions
2025-11-27 Adafruit Datalogger work (works now) and other
2025-11-28 Adding a second channel to the datalogger
2025-11-30 Work on the RP2040 logger and Open Lead Detect Meter
2025-11-30 Modified logger with adjustable trigger threshold.
2025-12-06 AdaLogger behavior improvements
    - Only one log file for both interval and triggered writes.
    - Logs are stamped with relative time since previous write in uS.
    - New auto data plotter version
2025-12-12 Cleanup of PCB files
2025-12-12 Working on Uno Form specific DMM
2025-12-12 Finished(?) an Uno footprint board, started on Feather specific
2025-12-18 Some V2 Isolator PCB work and some radio data tests
2025-12-20 Updating the datalogger to support an RTC module
2025-12-21 Adding an autoranging feature to the Adalogger voltmeter
2025-12-21 Revise ReadMe with updates on switches and battery
    Updated DIP switch description and added operating notes for shutting down the board. Revised battery monitoring section to clarify voltage display and added notes on log file creation and known limi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
2025-12-21 Added both a temp sensor and the "mark place" button for the log
2025-12-26 Some radio work. Adding circuit disable to open lead detect proof.
2025-12-27 Upgraded the Open-Lead Detect Circuit so bias voltage it can be turned on and off.
    This gives the option of either having the open lead detect, or a wider range without the upbiasing circuitry that puts a small signal into the device being probed.
2025-12-27 Working on next voltmeter PCB
2025-12-30 Programming Changes
    - More serial info in the Adalogger
    - Split Open Lead Detect Proof into the known-working MOSFET version, and a prototype not-working photo-MOSFET version.
    - Working on next Isolated ADS1X15 PCB
2026-01-05 Finishing a V2 of the ADS Isolated board. Radio Comm Board Program.
2026-01-11 Data Capture for Open Lead Detect, Swap Differential on AdaLogger
2026-01-17 Made a new logger version that can now do current and voltage simultaneously.
2026-01-18 Logger code and isolated voltmeter PCB adjustments
2026-01-19 Data Logger Version Now with Acceleration
2026-01-20 Updates for accel log threshold
2026-01-21 Minor programming updates
2026-02-01 Moved various files around for cleanup. Made Claude version of logger with improvements (beta)
2026-02-02 Made a new version of the Open Lead Detect Voltmeter that runs on an ESP32-S3 (with tft display)
2026-02-06 Added avg calc and optimized some parameters.
2026-02-07 Many improvements, including support for either an ADS1115 or ADS1015
2026-02-12 Various simple DMM / Scope work (including headless version)
2026-02-13 Improvements to the headless sketch and GUI
2026-02-16 Updated programs and worked on PCB designs...
2026-02-17 Added smoothing to generic voltmeter, and worked on AMC0330R PCB
2026-02-23 Various troubleshooting and PCB design
2026-02-26 Made a datalogger Android app and moved some datalogging files around
2026-03-07 Syncing Android Apps and various minor updates
2026-03-22 Made a datalogger version with larger TFT screen.
2026-04-19 Updates, see description
    Updated programming for open lead detect board
    worked on various PCBs, including a new open lead voltmeter design with few components
2026-04-19 Programmed a test board for some isolated readings
2026-04-20 Added in-progress CAN AMC test board
2026-05-25 Work on different PCBs. Mostly.
2026-05-25 More PCB work.
2026-05-29 PCB Work.
2026-05-31 DMM PCB work and Voltmeter Sketch Updates
2026-05-31 Circuits, mostly
2026-06-05 Giga Controller Updates
2026-06-05 More Giga GUI updates
2026-06-06 Giga GUI Improvements
2026-06-07 Many Giga GUI updates
2026-06-09 Many Giga Remote updates
2026-06-17 Misc project work over the last few days.
    LTSpice diff buffer design, some logger work, capturing data on my open-lead-detect circuit, designing a new open lead detect PCB.
2026-06-18 Open Lead Voltmeter now shows approx resistance
2026-06-20 Data Collection and minor revisions for Open Lead DMM
2026-06-21 More Open Lead Detect Diagnostic Work
2026-06-22 Lots of data collection, with some code updates on timings and thresholds.
2026-06-23 Further data collection and minor program edits.
2026-06-24 Minimal Open Lead Detect has a simpler board selection method.
